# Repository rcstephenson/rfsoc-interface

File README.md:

# RFSoC Breakout Board

This repo is for KiCAD6 projects replacing the FMC-XM500 daughter card with a smaller version using low frequency baluns and external differential clocking breakout board. 

## RFSoC_Frontend:

## RFSoC_directclocking:

---
signifigent contributions have been made by Eric Weeks and Cody Roberson at ASU to make this board operational.

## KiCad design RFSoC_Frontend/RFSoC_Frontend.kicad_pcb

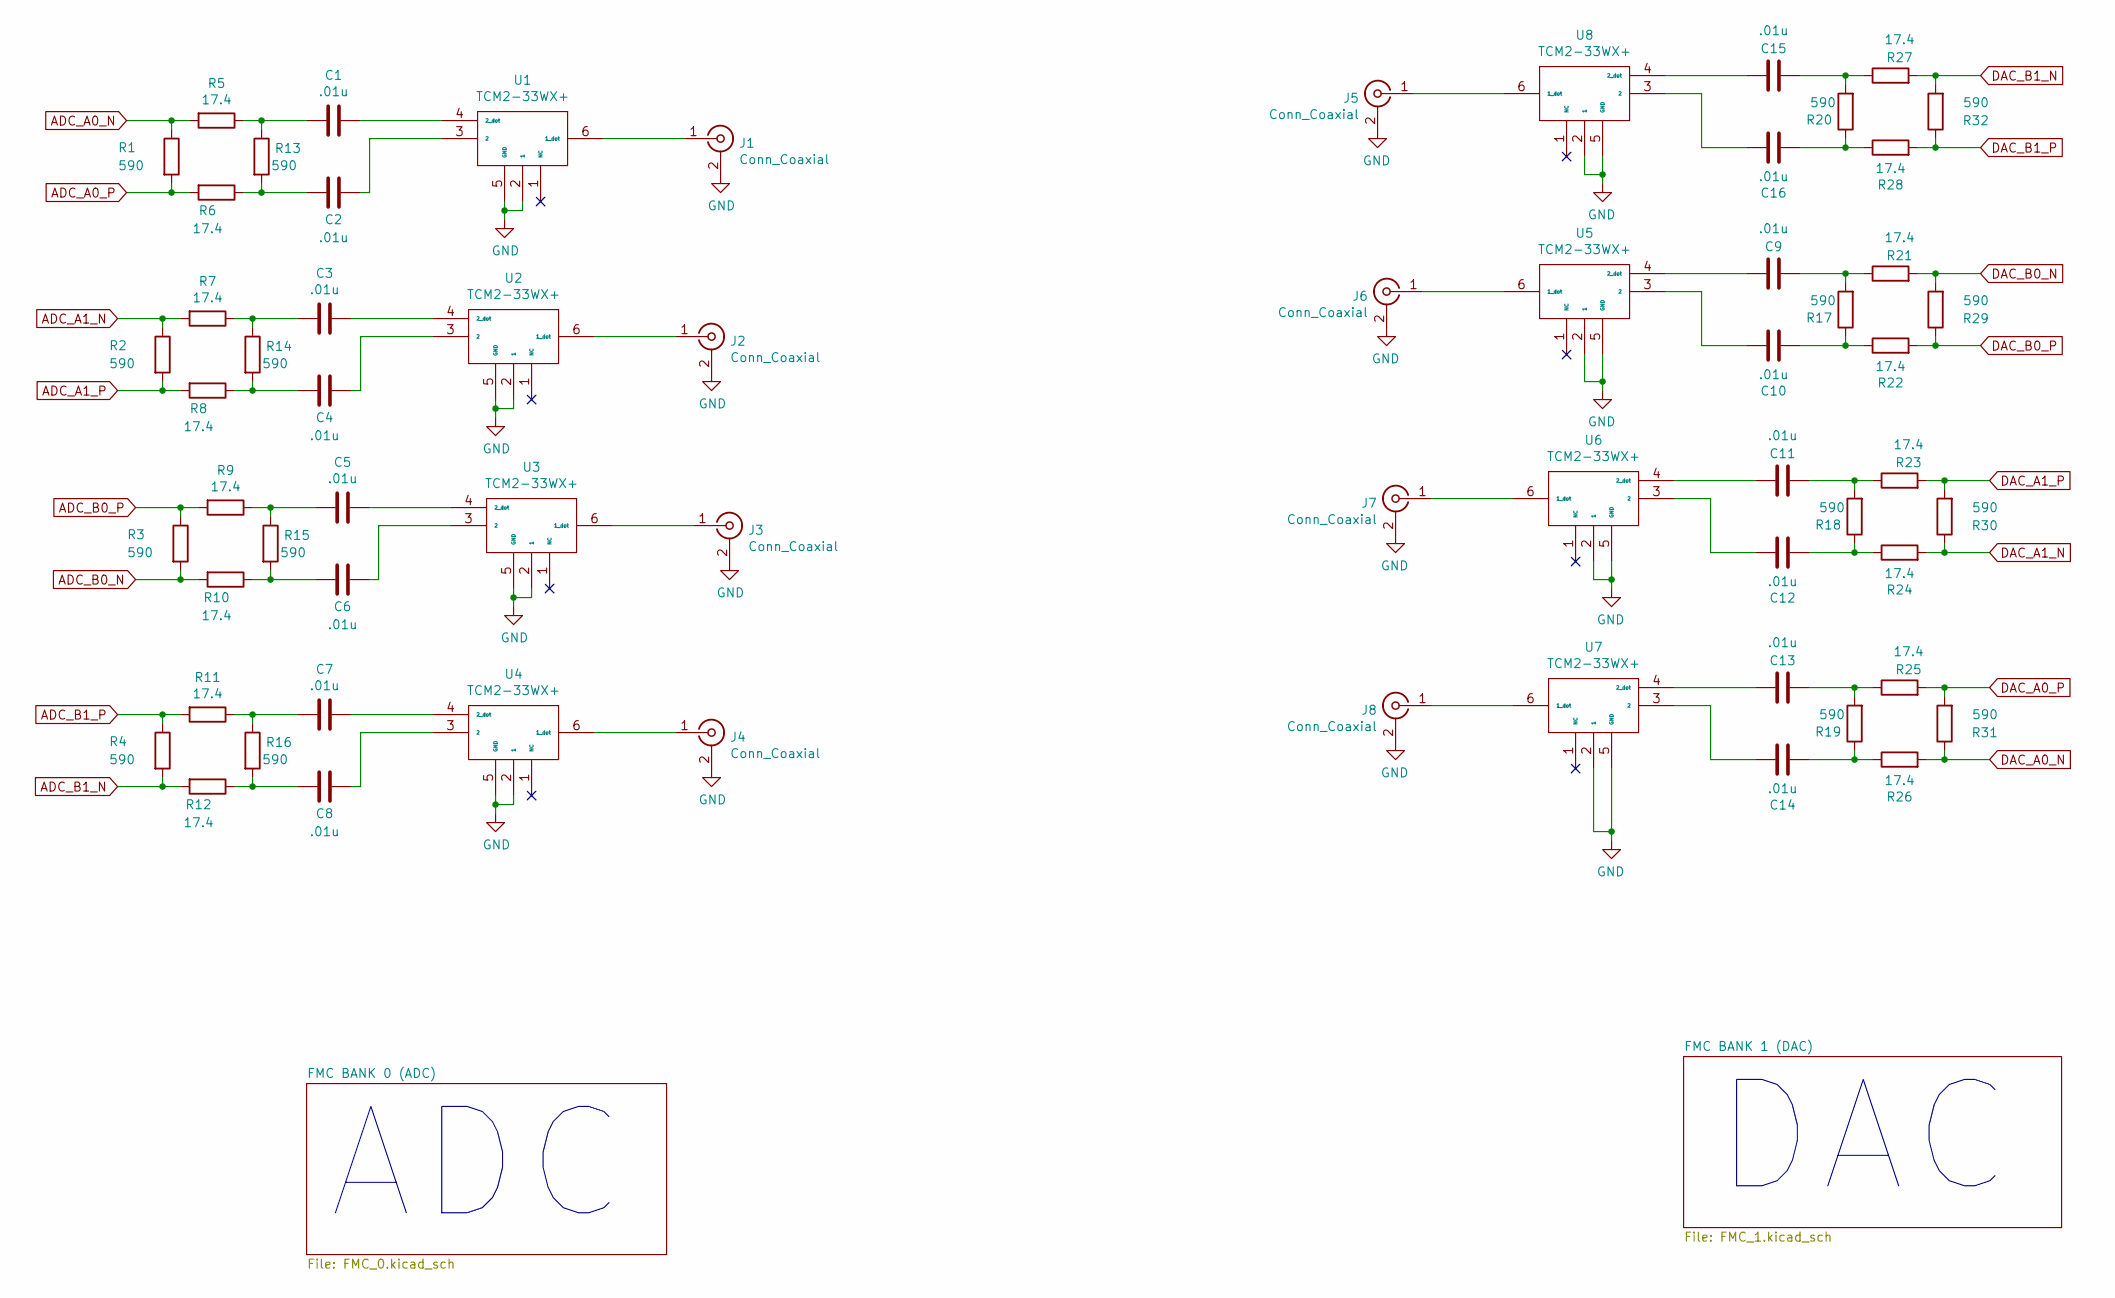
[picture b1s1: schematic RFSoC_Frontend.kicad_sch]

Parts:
C1, C2, C3, C4, C5, C6, C7, C8, C9, C10, C11, C12, C13, C14, C15, C16: .01u; C_0402_1005Metric
J1, J2, J3, J4, J5, J6, J7, J8: Conn_Coaxial; SMA_Amphenol_132289_EdgeMount
R1, R2, R3, R4, R13, R14, R15, R16, R17, R18, R19, R20, R29, R30, R31, R32: 590; R_0402_1005Metric
R5, R6, R7, R8, R9, R10, R11, R12, R21, R22, R23, R24, R25, R26, R27, R28: 17.4; R_0402_1005Metric
U1, U2, U3, U4, U5, U6, U7, U8: TCM2-33WX+; XFMR_TCM2-33WX+

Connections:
ADC_A0_N: R1.1, R5.2; also elsewhere on the board
ADC_A0_P: R1.2, R6.2; also elsewhere on the board
ADC_A1_N: R2.1, R7.2; also elsewhere on the board
ADC_A1_P: R2.2, R8.2; also elsewhere on the board
ADC_B0_N: R3.2, R10.2; also elsewhere on the board
ADC_B0_P: R3.1, R9.2; also elsewhere on the board
ADC_B1_N: R4.2, R12.2; also elsewhere on the board
ADC_B1_P: R4.1, R11.2; also elsewhere on the board
DAC_A0_N: R26.2, R31.1; also elsewhere on the board
DAC_A0_P: R25.2, R31.2; also elsewhere on the board
DAC_A1_N: R24.2, R30.1; also elsewhere on the board
DAC_A1_P: R23.2, R30.2; also elsewhere on the board
DAC_B0_N: R21.2, R29.2; also elsewhere on the board
DAC_B0_P: R22.2, R29.1; also elsewhere on the board
DAC_B1_N: R27.2, R32.2; also elsewhere on the board
DAC_B1_P: R28.2, R32.1; also elsewhere on the board
unnamed: C1.1, U1.4 (2_dot)
unnamed: C1.2, R5.1, R13.1
unnamed: C2.1, U1.3 (2)
unnamed: C2.2, R6.1, R13.2
unnamed: C3.1, U2.4 (2_dot)
unnamed: C3.2, R7.1, R14.1
unnamed: C4.1, U2.3 (2)
unnamed: C4.2, R8.1, R14.2
unnamed: C5.1, U3.4 (2_dot)
unnamed: C5.2, R9.1, R15.1
unnamed: C6.1, U3.3 (2)
unnamed: C6.2, R10.1, R15.2
unnamed: C7.1, U4.4 (2_dot)
unnamed: C7.2, R11.1, R16.1
unnamed: C8.1, U4.3 (2)
unnamed: C8.2, R12.1, R16.2
unnamed: C9.1, U5.4 (2_dot)
unnamed: C9.2, R17.2, R21.1
unnamed: C10.1, U5.3 (2)
unnamed: C10.2, R17.1, R22.1
unnamed: C11.1, U6.4 (2_dot)
unnamed: C11.2, R18.2, R23.1
unnamed: C12.1, U6.3 (2)
unnamed: C12.2, R18.1, R24.1
unnamed: C13.1, U7.4 (2_dot)
unnamed: C13.2, R19.2, R25.1
unnamed: C14.1, U7.3 (2)
unnamed: C14.2, R19.1, R26.1
unnamed: C15.1, U8.4 (2_dot)
unnamed: C15.2, R20.2, R27.1
unnamed: C16.1, U8.3 (2)
unnamed: C16.2, R20.1, R28.1
unnamed: J1.1 (In), U1.6 (1_dot)
unnamed: J2.1 (In), U2.6 (1_dot)
unnamed: J3.1 (In), U3.6 (1_dot)
unnamed: J4.1 (In), U4.6 (1_dot)
unnamed: J5.1 (In), U8.6 (1_dot)
unnamed: J6.1 (In), U5.6 (1_dot)
unnamed: J7.1 (In), U6.6 (1_dot)
unnamed: J8.1 (In), U7.6 (1_dot)

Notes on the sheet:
ADC
DAC

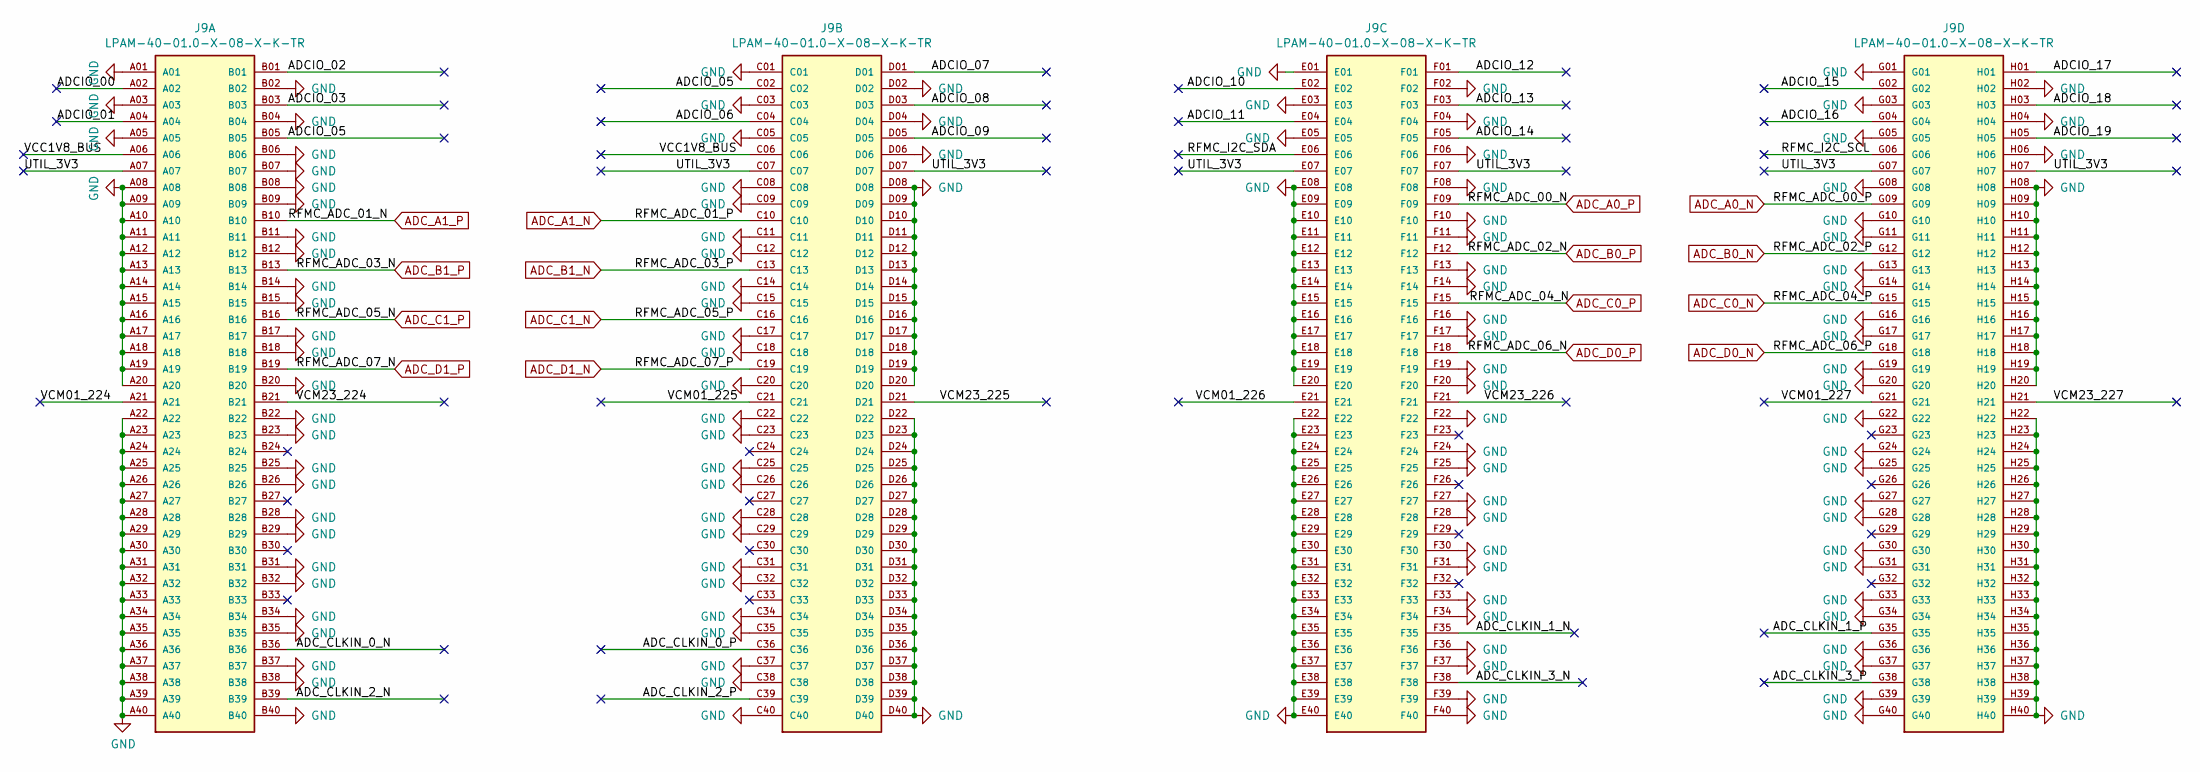
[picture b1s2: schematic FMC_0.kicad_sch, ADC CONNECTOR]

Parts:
J9: LPAM-40-01.0-X-08-X-K-TR; SAMTEC_LPAM-40-01.0-X-08-X-K-TR; PARTREV E

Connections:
/FMC BANK 0 (ADC)/ADCIO_00: J9.A02
/FMC BANK 0 (ADC)/ADCIO_01: J9.A04
/FMC BANK 0 (ADC)/ADCIO_02: J9.B01
/FMC BANK 0 (ADC)/ADCIO_03: J9.B03
/FMC BANK 0 (ADC)/ADCIO_05: J9.B05, J9.C02
/FMC BANK 0 (ADC)/ADCIO_06: J9.C04
/FMC BANK 0 (ADC)/ADCIO_07: J9.D01
/FMC BANK 0 (ADC)/ADCIO_08: J9.D03
/FMC BANK 0 (ADC)/ADCIO_09: J9.D05
/FMC BANK 0 (ADC)/ADCIO_10: J9.E02
/FMC BANK 0 (ADC)/ADCIO_11: J9.E04
/FMC BANK 0 (ADC)/ADCIO_12: J9.F01
/FMC BANK 0 (ADC)/ADCIO_13: J9.F03
/FMC BANK 0 (ADC)/ADCIO_14: J9.F05
/FMC BANK 0 (ADC)/ADCIO_15: J9.G02
/FMC BANK 0 (ADC)/ADCIO_16: J9.G04
/FMC BANK 0 (ADC)/ADCIO_17: J9.H01
/FMC BANK 0 (ADC)/ADCIO_18: J9.H03
/FMC BANK 0 (ADC)/ADCIO_19: J9.H05
/FMC BANK 0 (ADC)/ADC_CLKIN_0_N: J9.B36
/FMC BANK 0 (ADC)/ADC_CLKIN_0_P: J9.C36
/FMC BANK 0 (ADC)/ADC_CLKIN_1_N: J9.F35
/FMC BANK 0 (ADC)/ADC_CLKIN_1_P: J9.G35
/FMC BANK 0 (ADC)/ADC_CLKIN_2_N: J9.B39
/FMC BANK 0 (ADC)/ADC_CLKIN_2_P: J9.C39
/FMC BANK 0 (ADC)/ADC_CLKIN_3_N: J9.F38
/FMC BANK 0 (ADC)/ADC_CLKIN_3_P: J9.G38
/FMC BANK 0 (ADC)/RFMC_I2C_SCL: J9.G06
/FMC BANK 0 (ADC)/RFMC_I2C_SDA: J9.E06
/FMC BANK 0 (ADC)/UTIL_3V3: J9.A07, J9.C07, J9.D07, J9.E07, J9.F07, J9.G07, J9.H07
/FMC BANK 0 (ADC)/VCC1V8_BUS: J9.A06, J9.C06
/FMC BANK 0 (ADC)/VCM01_224: J9.A21
/FMC BANK 0 (ADC)/VCM01_225: J9.C21
/FMC BANK 0 (ADC)/VCM01_226: J9.E21
/FMC BANK 0 (ADC)/VCM01_227: J9.G21
/FMC BANK 0 (ADC)/VCM23_224: J9.B21
/FMC BANK 0 (ADC)/VCM23_225: J9.D21
/FMC BANK 0 (ADC)/VCM23_226: J9.F21
/FMC BANK 0 (ADC)/VCM23_227: J9.H21
ADC_A0_N: J9.G09; also elsewhere on the board
ADC_A0_P: J9.F09; also elsewhere on the board
ADC_A1_N: J9.C10; also elsewhere on the board
ADC_A1_P: J9.B10; also elsewhere on the board
ADC_B0_N: J9.G12; also elsewhere on the board
ADC_B0_P: J9.F12; also elsewhere on the board
ADC_B1_N: J9.C13; also elsewhere on the board
ADC_B1_P: J9.B13; also elsewhere on the board
ADC_C0_N: J9.G15
ADC_C0_P: J9.F15
ADC_C1_N: J9.C16
ADC_C1_P: J9.B16
ADC_D0_N: J9.G18
ADC_D0_P: J9.F18
ADC_D1_N: J9.C19
ADC_D1_P: J9.B19

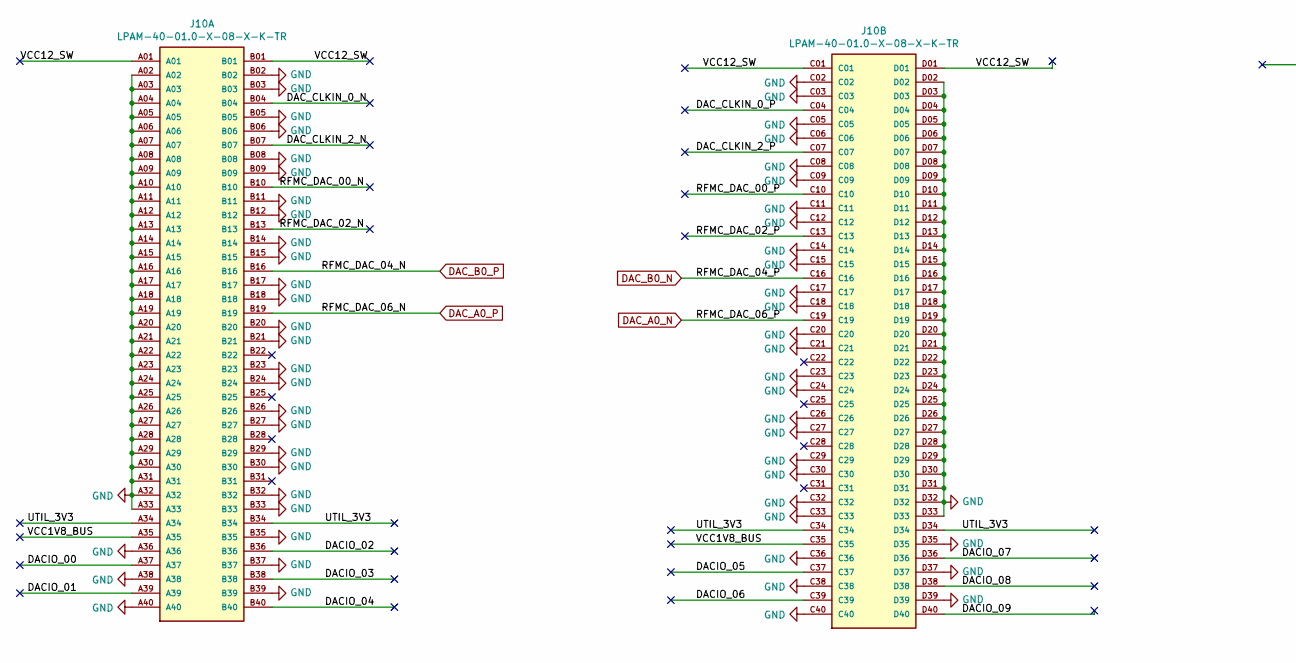
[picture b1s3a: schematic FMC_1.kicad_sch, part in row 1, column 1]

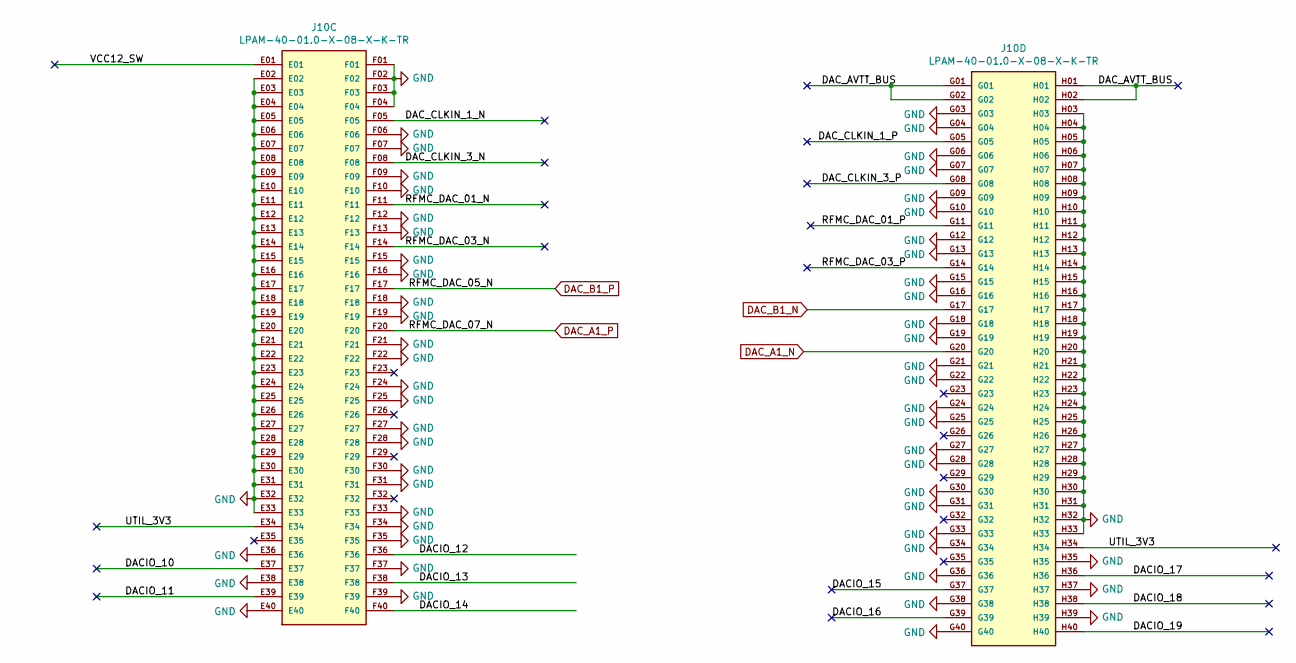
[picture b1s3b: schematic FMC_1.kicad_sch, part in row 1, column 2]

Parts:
J10: LPAM-40-01.0-X-08-X-K-TR; SAMTEC_LPAM-40-01.0-X-08-X-K-TR; PARTREV E

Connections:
/FMC BANK 1 (DAC)/DACIO_00: J10.A37
/FMC BANK 1 (DAC)/DACIO_01: J10.A39
/FMC BANK 1 (DAC)/DACIO_02: J10.B36
/FMC BANK 1 (DAC)/DACIO_03: J10.B38
/FMC BANK 1 (DAC)/DACIO_04: J10.B40
/FMC BANK 1 (DAC)/DACIO_05: J10.C37
/FMC BANK 1 (DAC)/DACIO_06: J10.C39
/FMC BANK 1 (DAC)/DACIO_07: J10.D36
/FMC BANK 1 (DAC)/DACIO_08: J10.D38
/FMC BANK 1 (DAC)/DACIO_09: J10.D40
/FMC BANK 1 (DAC)/DACIO_10: J10.E37
/FMC BANK 1 (DAC)/DACIO_11: J10.E39
/FMC BANK 1 (DAC)/DACIO_12: J10.F36
/FMC BANK 1 (DAC)/DACIO_13: J10.F38
/FMC BANK 1 (DAC)/DACIO_14: J10.F40
/FMC BANK 1 (DAC)/DACIO_15: J10.G37
/FMC BANK 1 (DAC)/DACIO_16: J10.G39
/FMC BANK 1 (DAC)/DACIO_17: J10.H36
/FMC BANK 1 (DAC)/DACIO_18: J10.H38
/FMC BANK 1 (DAC)/DACIO_19: J10.H40
/FMC BANK 1 (DAC)/DAC_AVTT_BUS: J10.G01, J10.G02, J10.H01, J10.H02
/FMC BANK 1 (DAC)/DAC_CLKIN_0_N: J10.B04
/FMC BANK 1 (DAC)/DAC_CLKIN_0_P: J10.C04
/FMC BANK 1 (DAC)/DAC_CLKIN_1_N: J10.F05
/FMC BANK 1 (DAC)/DAC_CLKIN_1_P: J10.G05
/FMC BANK 1 (DAC)/DAC_CLKIN_2_N: J10.B07
/FMC BANK 1 (DAC)/DAC_CLKIN_2_P: J10.C07
/FMC BANK 1 (DAC)/DAC_CLKIN_3_N: J10.F08
/FMC BANK 1 (DAC)/DAC_CLKIN_3_P: J10.G08
/FMC BANK 1 (DAC)/RFMC_DAC_00_N: J10.B10
/FMC BANK 1 (DAC)/RFMC_DAC_00_P: J10.C10
/FMC BANK 1 (DAC)/RFMC_DAC_01_N: J10.F11
/FMC BANK 1 (DAC)/RFMC_DAC_01_P: J10.G11
/FMC BANK 1 (DAC)/RFMC_DAC_02_N: J10.B13
/FMC BANK 1 (DAC)/RFMC_DAC_02_P: J10.C13
/FMC BANK 1 (DAC)/RFMC_DAC_03_N: J10.F14
/FMC BANK 1 (DAC)/RFMC_DAC_03_P: J10.G14
/FMC BANK 1 (DAC)/UTIL_3V3: J10.A34, J10.B34, J10.C34, J10.D34, J10.E34, J10.H34
/FMC BANK 1 (DAC)/VCC1V8_BUS: J10.A35, J10.C35
/FMC BANK 1 (DAC)/VCC12_SW: J10.A01, J10.B01, J10.C01, J10.D01, J10.E01
DAC_A0_N: J10.C19; also elsewhere on the board
DAC_A0_P: J10.B19; also elsewhere on the board
DAC_A1_N: J10.G20; also elsewhere on the board
DAC_A1_P: J10.F20; also elsewhere on the board
DAC_B0_N: J10.C16; also elsewhere on the board
DAC_B0_P: J10.B16; also elsewhere on the board
DAC_B1_N: J10.G17; also elsewhere on the board
DAC_B1_P: J10.F17; also elsewhere on the board

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
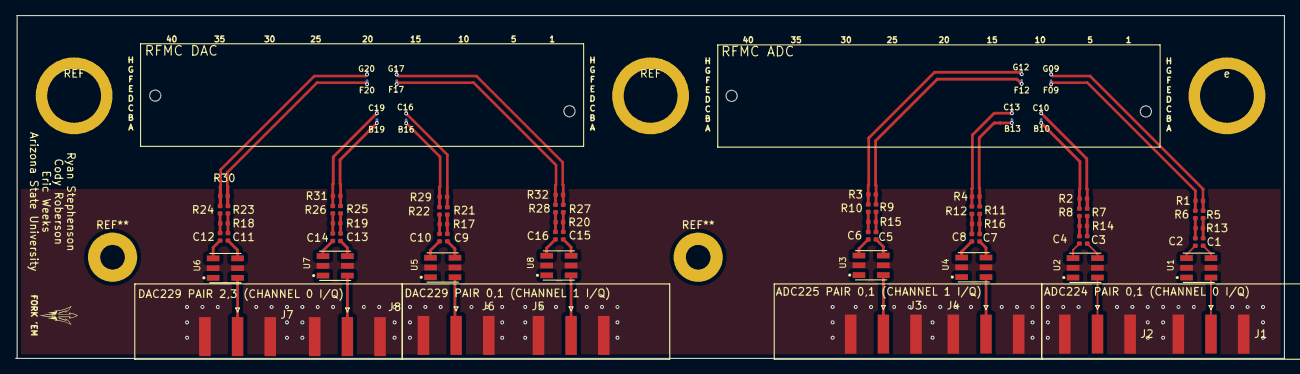
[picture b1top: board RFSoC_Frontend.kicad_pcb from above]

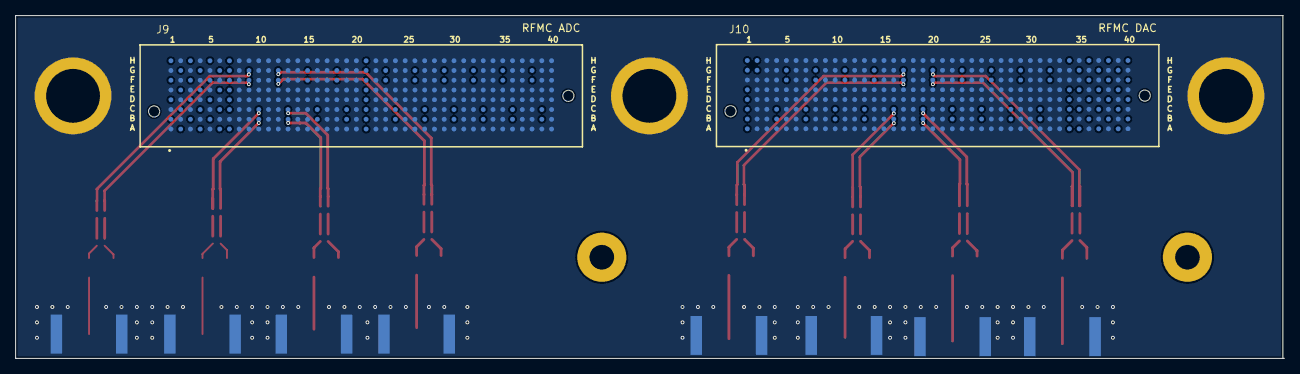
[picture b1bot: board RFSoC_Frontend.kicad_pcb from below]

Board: 4 copper layers, 165.1 x 44.6 mm, 69 parts (2 on the bottom side), 64 nets.

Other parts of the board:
REF: MountingHole_2.2mm_M2_DIN965_Pad
REF#2: MountingHole_2.2mm_M2_DIN965_Pad
e: MountingHole_2.2mm_M2_DIN965_Pad

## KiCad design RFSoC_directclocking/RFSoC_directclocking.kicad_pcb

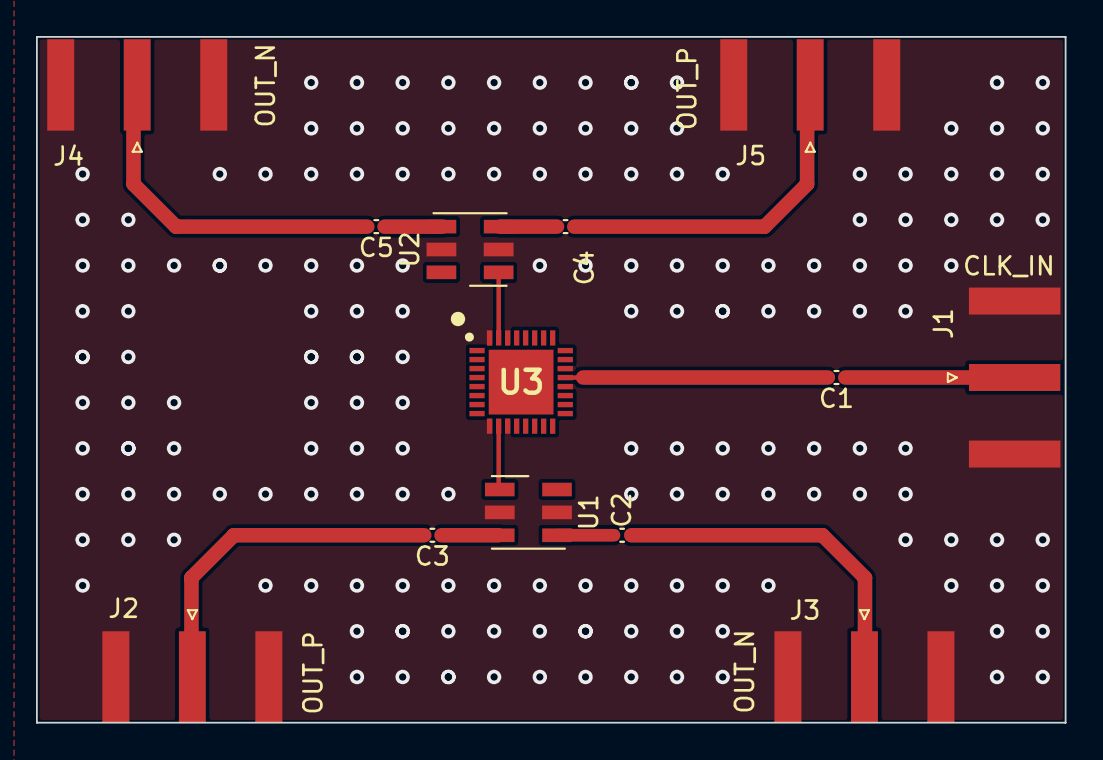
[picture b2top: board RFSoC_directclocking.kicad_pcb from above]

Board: 2 copper layers, 57.2 x 38.1 mm, 13 parts (0 on the bottom side), 13 nets.

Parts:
C1: C; C_0402_1005Metric
C2, C3, C4, C5: .01u; C_0402_1005Metric
J1, J2, J3, J4, J5: Conn_Coaxial; SMA_Amphenol_132289_EdgeMount
U1, U2: Mini-Circuits_DB1627
U3: EP2RCW+; QFN50P500X500X100-33N-D

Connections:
GND: J1.2 (Ext), J2.2 (Ext), J3.2 (Ext), J4.2 (Ext), J5.2 (Ext), U1.2 (1), U1.5 (GND), U2.2 (1), U2.5 (GND), U3.9 (GND), U3.11 (GND), U3.20 (GND), U3.22 (GND), U3.30 (GND), U3.32 (GND)
unnamed: C1.1, J1.1 (In)
unnamed: C1.2, U3.21 (RF_IN)
unnamed: C2.1, U1.3 (2)
unnamed: C2.2, J3.1 (In)
unnamed: C3.1, U1.4 (2_dot)
unnamed: C3.2, J2.1 (In)
unnamed: C4.1, U2.4 (2_dot)
unnamed: C4.2, J5.1 (In)
unnamed: C5.1, U2.3 (2)
unnamed: C5.2, J4.1 (In)
unnamed: U1.6 (1_dot), U3.10 (RF_OUT_1)
unnamed: U2.6 (1_dot), U3.31 (RFOUT2)

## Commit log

2021-10-20 init commit
2021-10-20 added readme
2021-10-26 resize board
2021-11-05 route differential lines
2022-02-23 added v1.0 board for kicad6
    first working version of RFSoC interface board for 2 channels bellow 1GHz
2022-02-23 fname fix
2022-03-07 add direct clocking board
    this design is to break out a single clock line into 2 differential lines to drive a DAC-ADC pair
2022-03-09 mc lib components
2022-03-09 added kicad symbol for power splitter
2022-03-09 sym rename
2022-03-09 added kicad symbol+footprint
2022-03-09 improvements
    Made improvement to kicad symbol and replaced footprint for baluns. They
    were incorrectly orientated with regards to pin numbering
2022-03-10 moved forkem and labeled ports
2022-03-10 finalized version for order placement
2022-03-14 pmod board update
2022-05-05 partial update of labels
2022-05-09 progress check
    Started Labeling process
2022-05-09 Finished Updated ADC schematic
    ADC schematic was modified to match the pin map between
    the rfsoc and the xm500.
2022-05-13 updated all
2022-05-13 fork em
2022-05-15 updated silkscreens, degin DRC corrections
2022-06-09 Squashed commit of the following:
    commit 11c362fd04afcdda8fc54016fc262973d8ee90dd
    Author: cody <you@example.com>
    Date: Sat May 14 20:18:42 2022 -0700
    updated silkscreens, degin DRC corrections
    commit c03c76887280f84603892cf274eefb7fb13b0fa8
    Author: cody <you@example.com>
2022-06-09 merging changes from @codyroberson
    Changes include Cody and Eric's modification of the rf breakout board, and direct rf clock board.
2022-06-17 deleted unused files
2022-06-17 added board.png and updated info
